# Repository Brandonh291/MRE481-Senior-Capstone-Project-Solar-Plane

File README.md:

# MRE481-Senior-Capstone-Project-Solar-Plane

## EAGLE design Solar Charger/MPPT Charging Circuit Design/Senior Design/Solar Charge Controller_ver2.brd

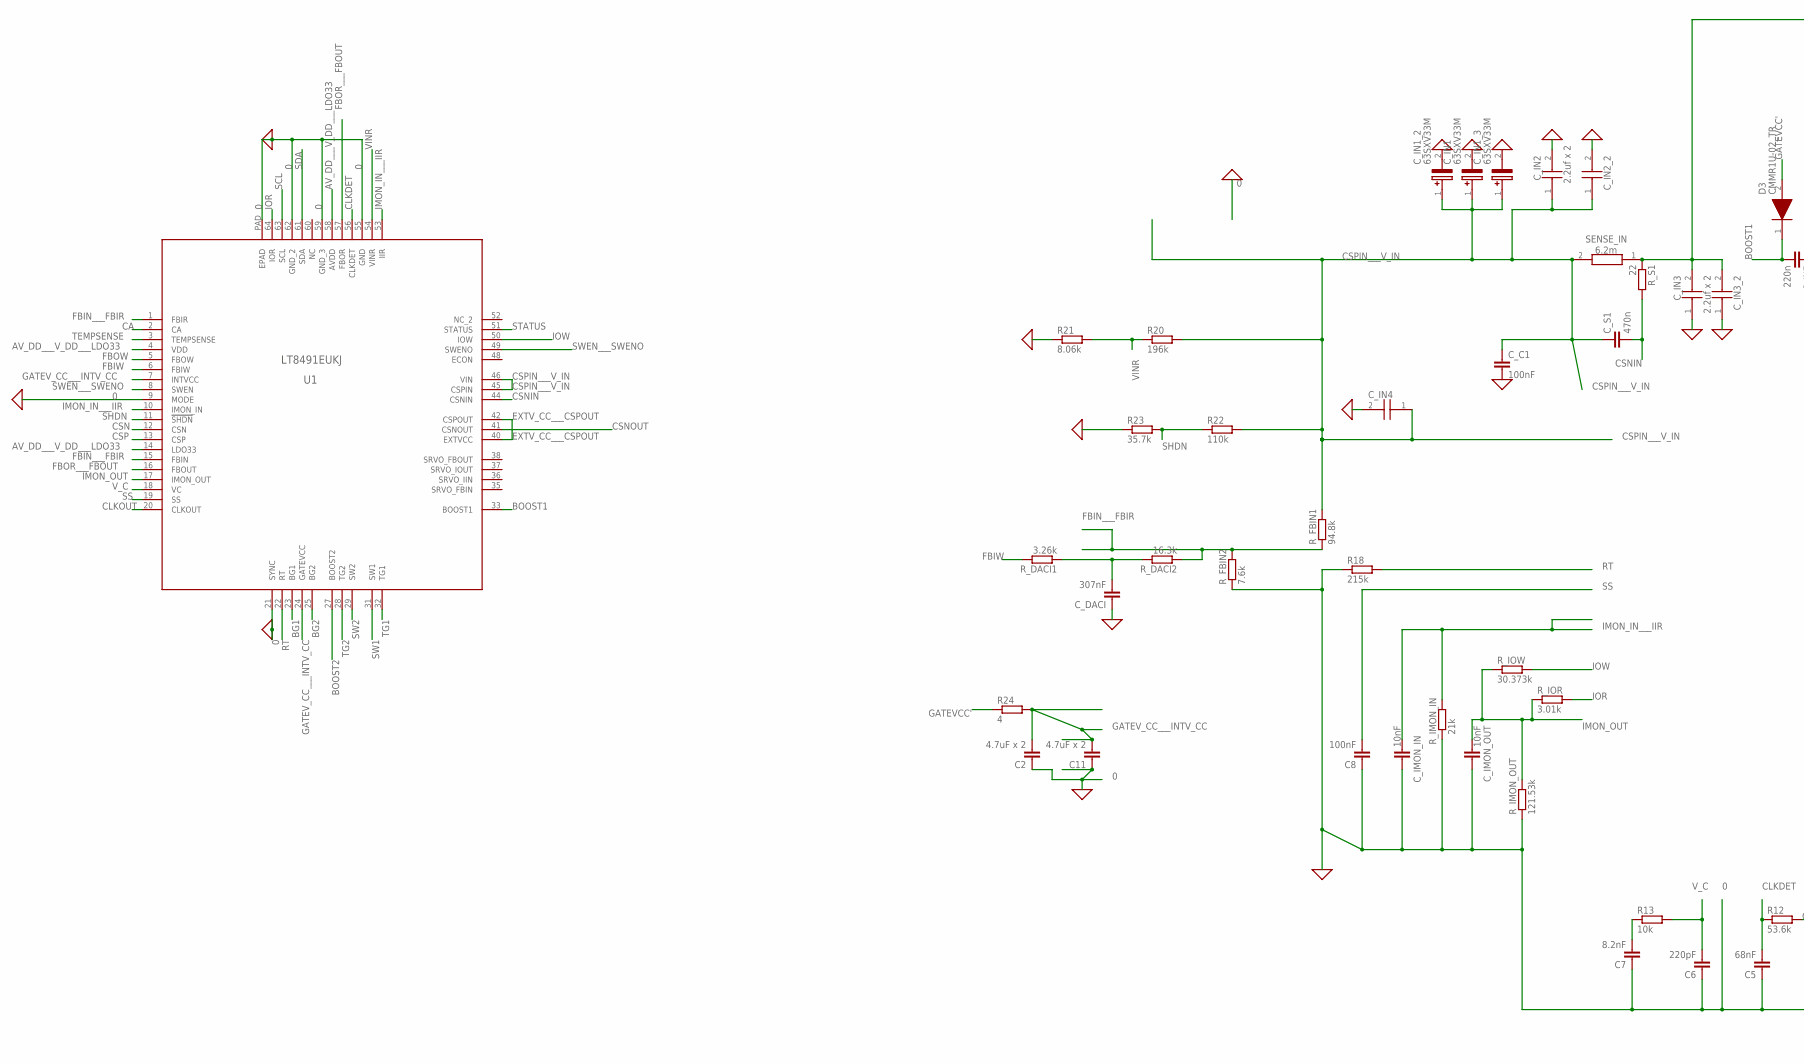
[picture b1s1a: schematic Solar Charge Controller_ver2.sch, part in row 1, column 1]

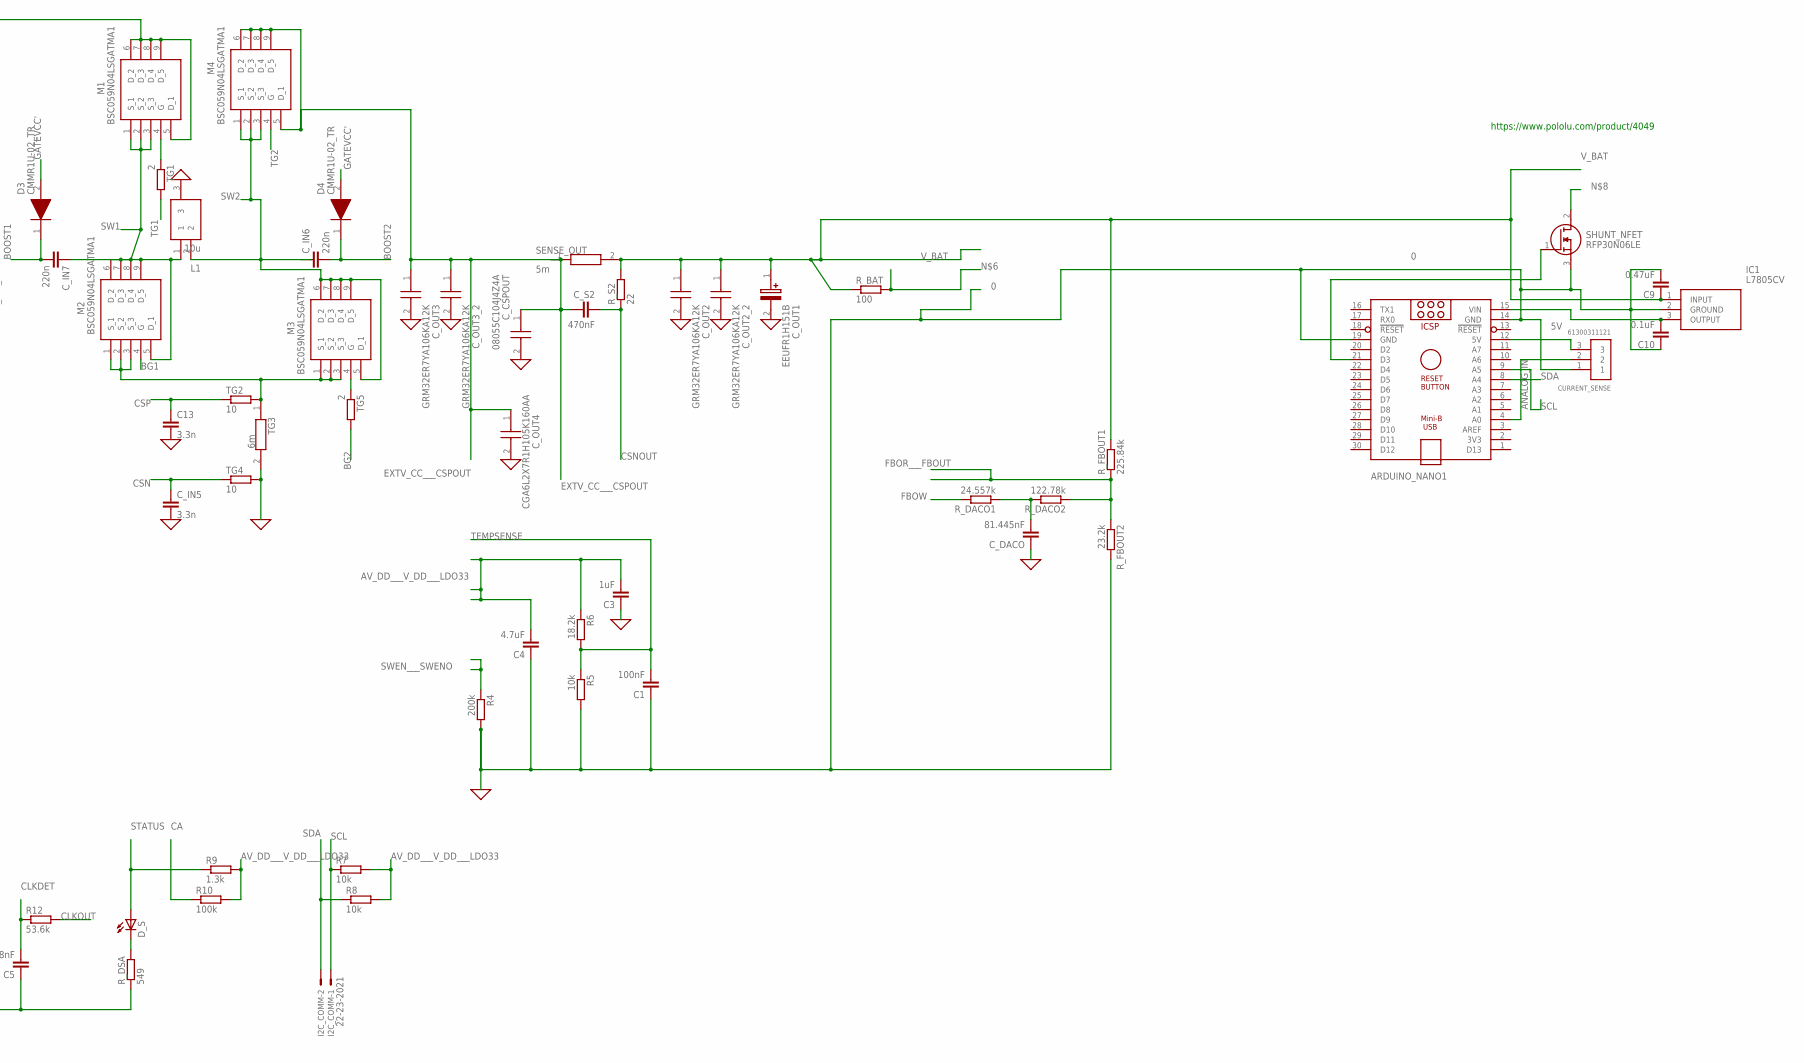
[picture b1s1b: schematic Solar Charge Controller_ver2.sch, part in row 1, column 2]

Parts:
ARDUINO_NANO1: ARDUINO_NANO
C1, C8: 100nF; C1206
C2, C11: 4.7uF x 2; C1206
C3: 1uF; C1206
C4: 4.7uF; C1206
C5: 68nF; C0603
C6: 220pF; C1206
C7: 8.2nF; C1206
C9: 0.47uF; C1206
C10: 0.1uF; C1206
C13: 3.3n; C1206
CURRENT_SENSE: 61300311121
C_C1: 100nF; C1206
C_CSPOUT: 08055C104J4Z4A; CAPC2012X127N
C_DACI: 307nF; C1206
C_DACO: 81.445nF; C1206
C_IMON_IN: 10nF; C1206
C_IMON_OUT: 10nF; C1206
C_IN1, C_IN1_2, C_IN1_3: 63SXV33M; CAPAE830X1200N
C_IN2, C_IN2_2, C_IN3, C_IN3_2: 2.2uf x 2; CAPC3325X279N
C_IN4: 2.2uf; CAPC3325X279N
C_IN5: 3.3n; C1206
C_IN6, C_IN7: 220n; C1206
C_OUT1: EEUFR1H151B; CAPPRD500W65D1000H1400
C_OUT2, C_OUT2_2, C_OUT3, C_OUT3_2: GRM32ER7YA106KA12K; CAPC3225X270N
C_OUT4: CGA6L2X7R1H105K160AA; CAPC3225X280N
C_S1: 470n; C1206
C_S2: 470nF; C1206
D3, D4: CMMR1U-02_TR; SODFL3818X108N
D_S: LED_E; LED_1206
I2C_COMM: 22-23-2021
IC1: L7805CV; TO255P460X1020X2008-3P
L1: 10u; SER2900
M1, M2, M3, M4: BSC059N04LSGATMA1; BSC080N03LSG
R4: 200k; R1206
R5, R7, R8, R13: 10k; R1206
R6: 18.2k; R1206
R9: 1.3k; R1206
R10: 100k; R1206
R12: 53.6k; R1206
R18: 215k; R1206
R20: 196k; R1206
R21: 8.06k; R1206
R22: 110k; R1206
R23: 35.7k; R1206
R24: 4; R1206
R_BAT: 100; R1206
R_DACI1: 3.26k; R1206
R_DACI2: 16.3k; R1206
R_DACO1: 24.557k; R1206
R_DACO2: 122.78k; R1206
R_DSA: 549; R1206
R_FBIN1: 94.8k; R1206
R_FBIN2: 7.6k; R1206
R_FBOUT1: 225.84k; R1206
R_FBOUT2: 23.2k; R1206
R_IMON_IN: 21k; R1206
R_IMON_OUT: 121.53k; R1206
R_IOR: 3.01k; R1206
R_IOW: 30.373k; R1206
R_S1, R_S2: 22; R1206
SENSE_IN: 6.2m; RESC2012X80N
SENSE_OUT: 5m; RESC3216X89N
SHUNT_NFET: RFP30N06LE; TO254P470X1016X2019-3P
TG1, TG5: 2; R1206
TG2, TG4: 10; R1206
TG3: 6m; RESC2012X80N
U1: LT8491EUKJ; QFN64(58)-UKJ-REV0_ADI

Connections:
0: ARDUINO_NANO1.14 (GND), ARDUINO_NANO1.19 (GND), C1.1, C2.1, C3.1, C4.1, C5.1, C6.1, C7.1, C8.1, C9.2, C10.1, C11.1, C13.2, CURRENT_SENSE.1, C_C1.2, C_CSPOUT.2, C_DACI.1, C_DACO.1, C_IMON_IN.1, C_IMON_OUT.1, C_IN1.2 (-), C_IN1_2.2 (-), C_IN1_3.2 (-), C_IN2.2, C_IN2_2.2, C_IN3.1, C_IN3_2.1, C_IN4.2, C_IN5.2, C_OUT1.2 (-), C_OUT2.2, C_OUT2_2.2, C_OUT3.2, C_OUT3_2.2, C_OUT4.2, IC1.2 (GROUND), L1.3, R4.2, R5.2, R18.1, R21.1, R23.1, R_DSA.1, R_FBIN2.1, R_FBOUT2.2, R_IMON_IN.1, R_IMON_OUT.1, SHUNT_NFET.3 (S), TG3.2, TG4.2, U1.9 (MODE), U1.21 (SYNC), U1.55 (GND), U1.59 (GND_3), U1.62 (GND_2), U1.PAD (EPAD)
5V: ARDUINO_NANO1.12 (5V), CURRENT_SENSE.3
ANALOG_IN: ARDUINO_NANO1.4 (A0), CURRENT_SENSE.2
AV_DD___V_DD___LDO33: C3.2, C4.2, R6.1, R7.2, R8.2, R9.2, R10.2, U1.4 (VDD), U1.14 (LDO33), U1.58 (AVDD)
BG1: M2.4 (G), U1.23 (BG1)
BG2: TG5.2, U1.25 (BG2)
BOOST1: C_IN7.2, D3.1 (K), U1.33 (BOOST1)
BOOST2: C_IN6.2, D4.1 (K), U1.27 (BOOST2)
CA: R10.1, U1.2 (CA)
CLKDET: C5.2, R12.1, U1.56 (CLKDET)
CLKOUT: R12.2, U1.20 (CLKOUT)
CSN: C_IN5.1, TG4.1, U1.12 (CSN)
CSNIN: C_S1.2, R_S1.2, U1.44 (CSNIN)
CSNOUT: C_S2.2, R_S2.1, U1.41 (CSNOUT)
CSP: C13.1, TG2.1, U1.13 (CSP)
CSPIN___V_IN: C_C1.1, C_IN1.1 (+), C_IN1_2.1 (+), C_IN1_3.1 (+), C_IN2.1, C_IN2_2.1, C_IN4.1, C_S1.1, R20.2, R22.2, R_FBIN1.2, SENSE_IN.2, U1.45 (CSPIN), U1.46 (VIN)
EXTV_CC___CSPOUT: C_CSPOUT.1, C_OUT3.1, C_OUT3_2.1, C_OUT4.1, C_S2.1, M4.5 (D_1), M4.6 (D_2), M4.7 (D_3), M4.8 (D_4), M4.9 (D_5), SENSE_OUT.1, U1.40 (EXTVCC), U1.42 (CSPOUT)
FBIN___FBIR: R_DACI2.1, R_FBIN1.1, R_FBIN2.2, U1.1 (FBIR), U1.15 (FBIN)
FBIW: R_DACI1.2, U1.6 (FBIW)
FBOR___FBOUT: R_DACO2.1, R_FBOUT1.1, R_FBOUT2.1, U1.16 (FBOUT), U1.57 (FBOR)
FBOW: R_DACO1.2, U1.5 (FBOW)
GATEVCC': D3.2 (A), D4.2 (A), R24.1
GATEV_CC___INTV_CC: C2.2, C11.2, R24.2, U1.7 (INTVCC), U1.24 (GATEVCC)
IMON_IN___IIR: C_IMON_IN.2, R_IMON_IN.2, U1.10 (IMON_IN), U1.53 (IIR)
IMON_OUT: C_IMON_OUT.2, R_IMON_OUT.2, R_IOR.1, R_IOW.1, U1.17 (IMON_OUT)
IOR: R_IOR.2, U1.64 (IOR)
IOW: R_IOW.2, U1.50 (IOW)
unnamed: C_IN3.2, C_IN3_2.2, M1.5 (D_1), M1.6 (D_2), M1.7 (D_3), M1.8 (D_4), M1.9 (D_5), R_S1.1, SENSE_IN.1
unnamed: M2.1 (S_1), M2.2 (S_2), M2.3 (S_3), M3.1 (S_1), M3.2 (S_2), M3.3 (S_3), TG2.2, TG3.1
unnamed: M1.4 (G), TG1.1
unnamed: C_DACI.2, R_DACI1.1, R_DACI2.2
unnamed: M3.4 (G), TG5.1
unnamed: ARDUINO_NANO1.15 (VIN), C10.2, IC1.3 (OUTPUT)
unnamed: ARDUINO_NANO1.21 (D3), SHUNT_NFET.1 (G)
unnamed: C_DACO.2, R_DACO1.1, R_DACO2.2
unnamed: D_S.C, R_DSA.2
unnamed: C7.2, R13.1
RT: R18.2, U1.22 (RT)
SCL: ARDUINO_NANO1.9 (A5), I2C_COMM.1, R7.1, U1.63 (SCL)
SDA: ARDUINO_NANO1.8 (A4), I2C_COMM.2, R8.1, U1.61 (SDA)
SHDN: R22.1, R23.2, U1.11 (!SHDN)
SS: C8.2, U1.19 (SS)
STATUS: D_S.A, R9.1, U1.51 (STATUS)
SW1: C_IN7.1, L1.1, M1.1 (S_1), M1.2 (S_2), M1.3 (S_3), M2.5 (D_1), M2.6 (D_2), M2.7 (D_3), M2.8 (D_4), M2.9 (D_5), U1.31 (SW1)
SW2: C_IN6.1, L1.2, M3.5 (D_1), M3.6 (D_2), M3.7 (D_3), M3.8 (D_4), M3.9 (D_5), M4.1 (S_1), M4.2 (S_2), M4.3 (S_3), U1.29 (SW2)
SWEN___SWENO: R4.1, U1.8 (SWEN), U1.49 (SWENO)
TEMPSENSE: C1.2, R5.1, R6.2, U1.3 (TEMPSENSE)
TG1: TG1.2, U1.32 (TG1)
TG2: M4.4 (G), U1.28 (TG2)
VINR: R20.1, R21.2, U1.54 (VINR)
V_BAT: C9.1, C_OUT1.1 (+), C_OUT2.1, C_OUT2_2.1, IC1.1 (INPUT), R_BAT.1, R_FBOUT1.2, R_S2.2, SENSE_OUT.2
V_C: C6.2, R13.2, U1.18 (VC)

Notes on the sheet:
https://www.pololu.com/product/4049

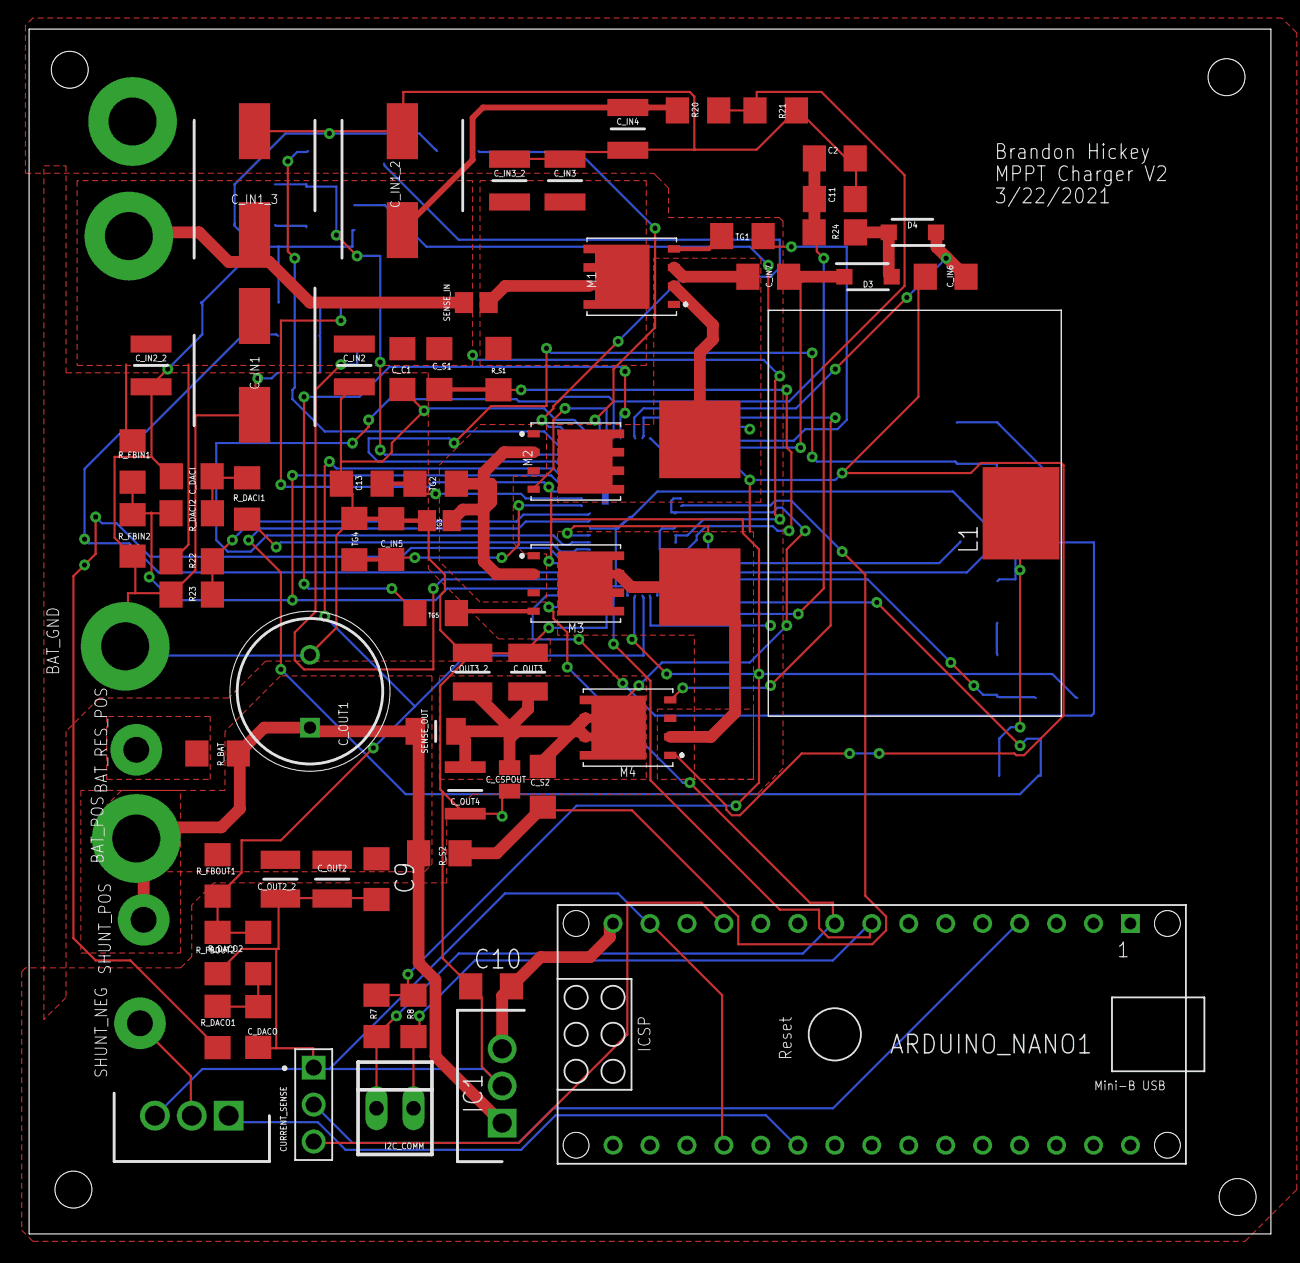
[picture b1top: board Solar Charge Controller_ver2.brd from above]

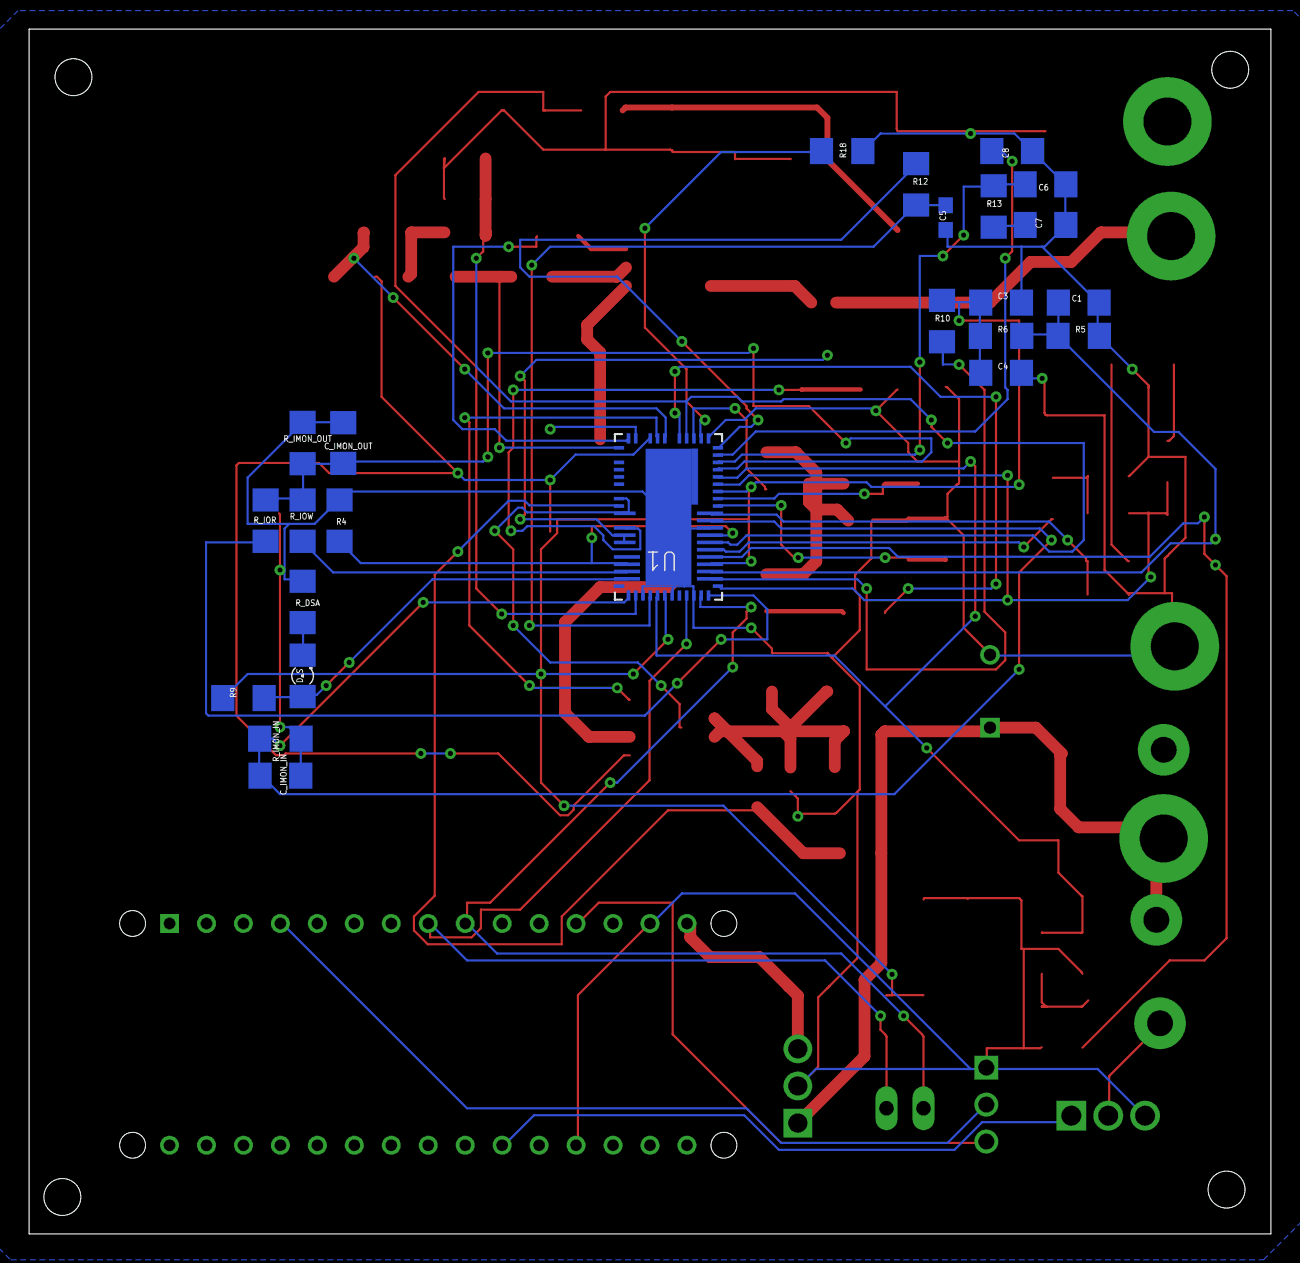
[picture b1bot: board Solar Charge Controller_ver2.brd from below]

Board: 2 copper layers, 85.3 x 82.8 mm, 89 parts (24 on the bottom side), 52 nets.

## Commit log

2023-08-01 Adding All-together

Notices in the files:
parts and their libraries:
COPYRIGHT: Copyright (C) 2018 Accelerated Designs. All rights reserved
